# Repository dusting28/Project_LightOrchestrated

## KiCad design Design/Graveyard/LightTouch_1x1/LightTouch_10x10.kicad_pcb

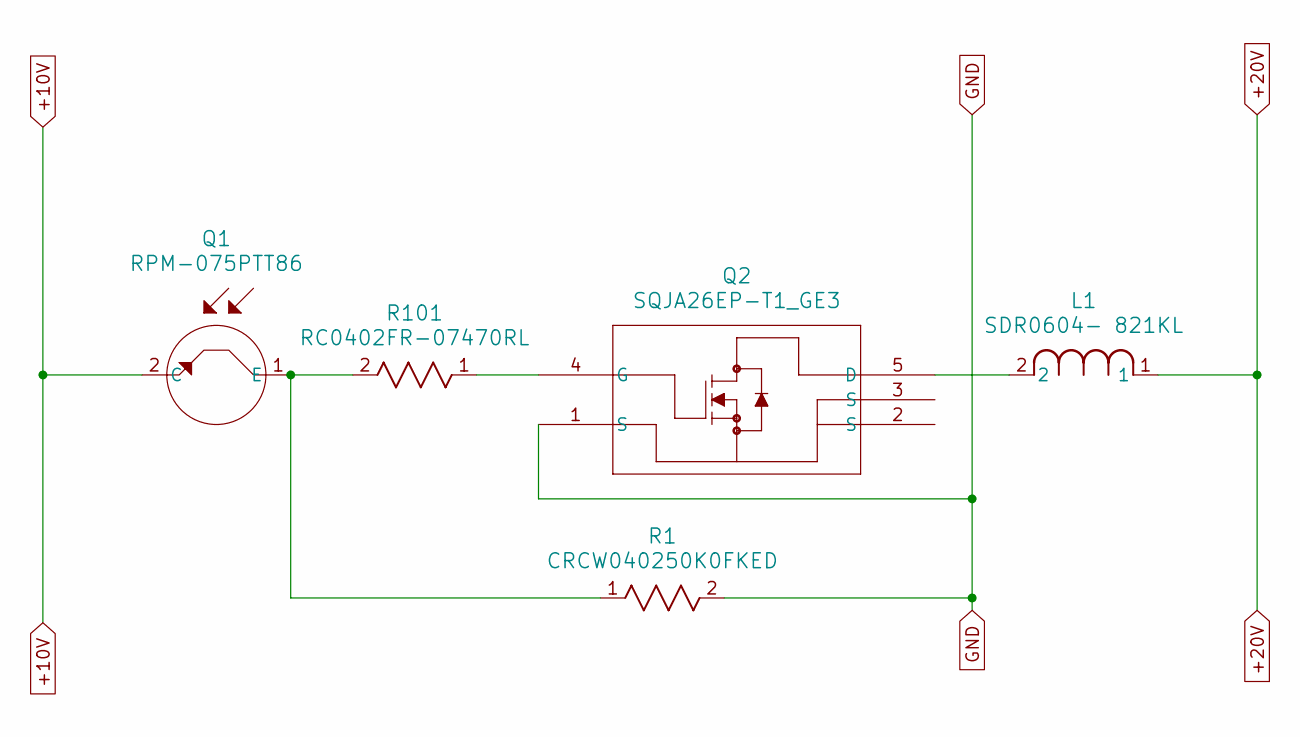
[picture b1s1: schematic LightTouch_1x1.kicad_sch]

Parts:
L1: SDR0604- 821KL; IND_BOURNS_SDR0604
Q1: RPM-075PTT86; TRANS_RPM-075P_ROM
Q2: SQJA26EP-T1_GE3; PowerPAK_SO-8L_3_VIS
R1: CRCW040250K0FKED; RES_CRCW0402_VIS
R101: RC0402FR-07470RL; RC0402N_YAG

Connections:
+10V: Q1.2 (C)
+20V: L1.1
GND: Q2.1 (S), R1.2
unnamed: Q1.1 (E), R1.1, R101.2
unnamed: L1.2, Q2.5 (D)
unnamed: Q2.4 (G), R101.1

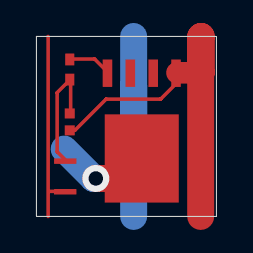
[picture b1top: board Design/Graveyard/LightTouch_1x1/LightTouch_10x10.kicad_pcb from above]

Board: 2 copper layers, 10.0 x 10.0 mm, 5 parts (1 on the bottom side), 4 nets.

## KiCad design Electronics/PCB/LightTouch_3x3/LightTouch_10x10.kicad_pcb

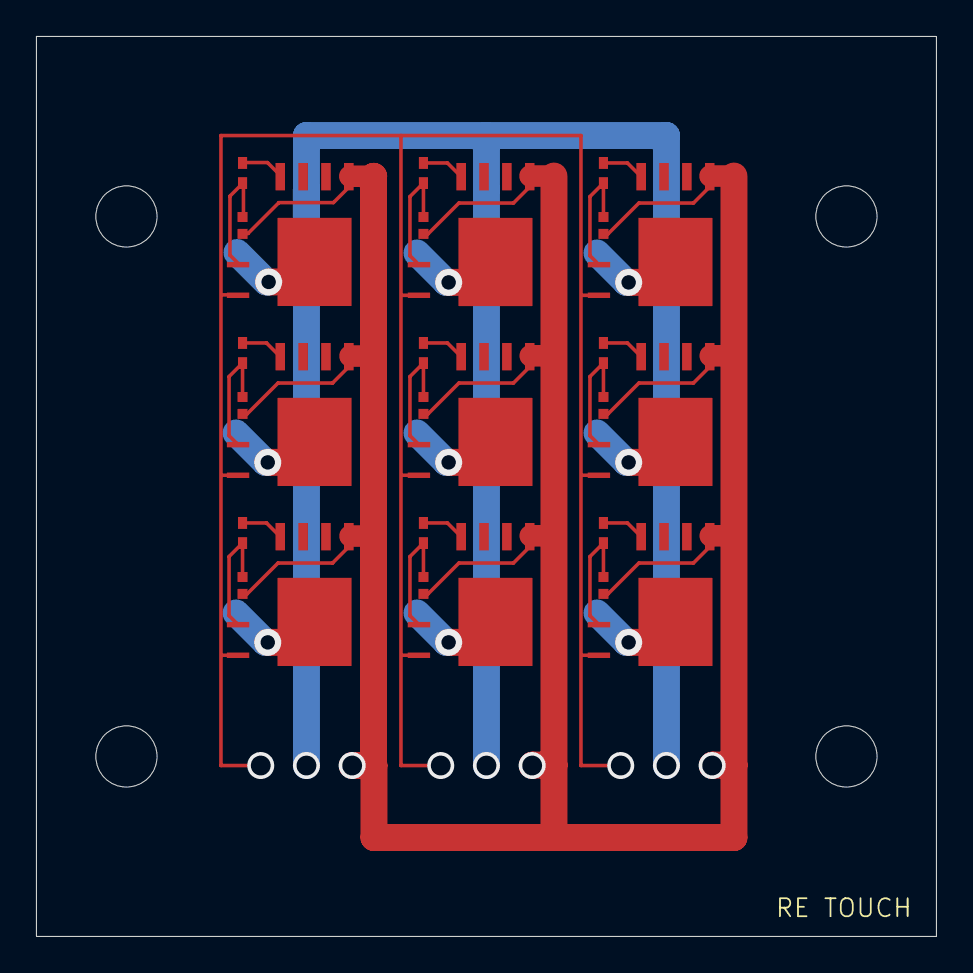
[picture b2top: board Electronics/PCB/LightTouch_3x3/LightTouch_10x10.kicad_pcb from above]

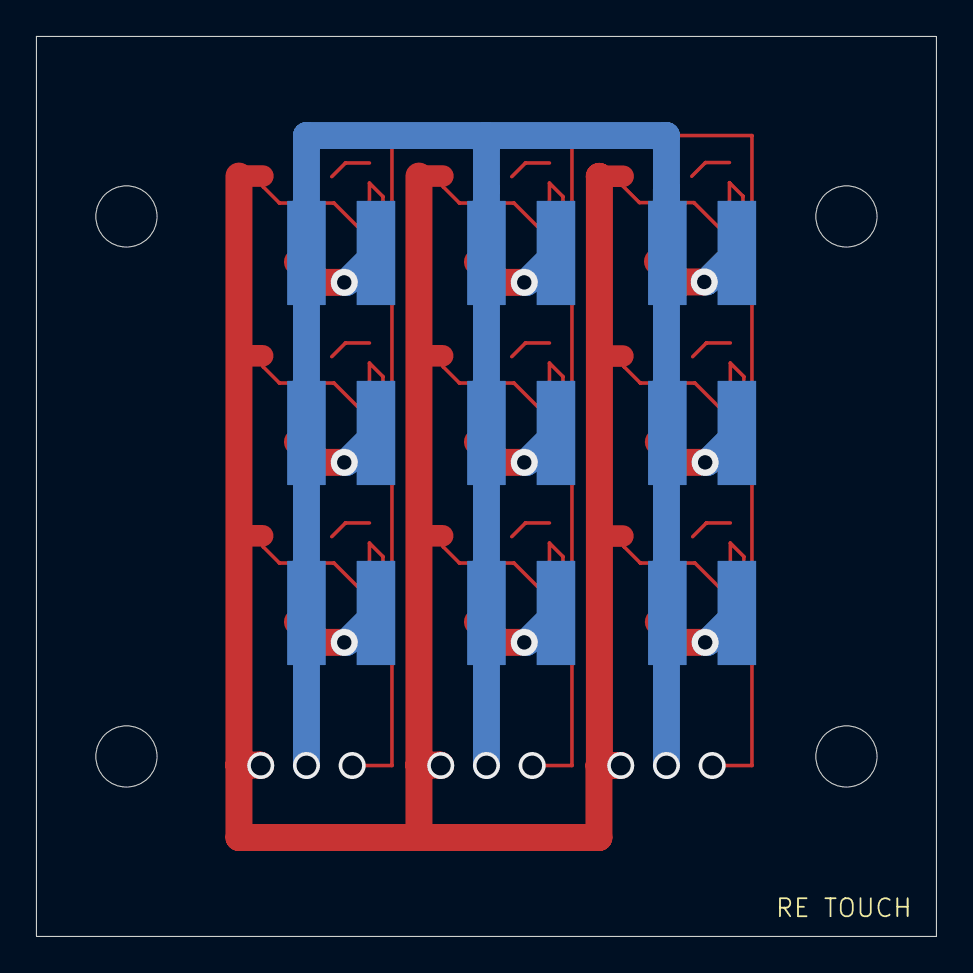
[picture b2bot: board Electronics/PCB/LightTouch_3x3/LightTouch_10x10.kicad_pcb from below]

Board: 2 copper layers, 50.0 x 50.0 mm, 45 parts (9 on the bottom side), 30 nets.

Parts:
L1, L2, L3, L4, L5, L6, L7, L8, L9: SDR0604- 821KL; IND_BOURNS_SDR0604
Q1, Q3, Q5, Q7, Q9, Q11, Q13, Q15, Q17: RPM-075PTT86; TRANS_RPM-075P_ROM
Q2, Q4, Q6, Q8, Q10, Q12, Q14, Q16, Q18: SQJA26EP-T1_GE3; PowerPAK_SO-8L_3_VIS
R1, R2, R3, R4, R5, R6, R7, R8, R9: CRCW040250K0FKED; RES_CRCW0402_VIS
R101, R102, R103, R104, R105, R106, R107, R108, R109: RC0402FR-07470RL; RC0402N_YAG

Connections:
+10V: Q1.2 (C), Q3.2 (C), Q5.2 (C), Q7.2 (C), Q9.2 (C), Q11.2 (C), Q13.2 (C), Q15.2 (C), Q17.2 (C)
+20V: L1.1, L2.1, L3.1, L4.1, L5.1, L6.1, L7.1, L8.1, L9.1
GND: Q2.1 (S), Q4.1 (S), Q6.1 (S), Q8.1 (S), Q10.1 (S), Q12.1 (S), Q14.1 (S), Q16.1 (S), Q18.1 (S), R1.2, R2.2, R3.2, R4.2, R5.2, R6.2, R7.2, R8.2, R9.2
unnamed: Q1.1 (E), R1.1, R101.2
unnamed: L1.2, Q2.5 (D)
unnamed: Q2.4 (G), R101.1
unnamed: Q3.1 (E), R2.1, R102.2
unnamed: L2.2, Q4.5 (D)
unnamed: Q4.4 (G), R102.1
unnamed: Q5.1 (E), R3.1, R103.2
unnamed: L3.2, Q6.5 (D)
unnamed: Q6.4 (G), R103.1
unnamed: Q7.1 (E), R4.1, R104.2
unnamed: L4.2, Q8.5 (D)
unnamed: Q8.4 (G), R104.1
unnamed: Q9.1 (E), R5.1, R105.2
unnamed: L5.2, Q10.5 (D)
unnamed: Q10.4 (G), R105.1
unnamed: Q11.1 (E), R6.1, R106.2
unnamed: L6.2, Q12.5 (D)
unnamed: Q12.4 (G), R106.1
unnamed: Q13.1 (E), R7.1, R107.2
unnamed: L7.2, Q14.5 (D)
unnamed: Q14.4 (G), R107.1
unnamed: Q15.1 (E), R8.1, R108.2
unnamed: L8.2, Q16.5 (D)
unnamed: Q16.4 (G), R108.1
unnamed: Q17.1 (E), R9.1, R109.2
unnamed: L9.2, Q18.5 (D)
unnamed: Q18.4 (G), R109.1

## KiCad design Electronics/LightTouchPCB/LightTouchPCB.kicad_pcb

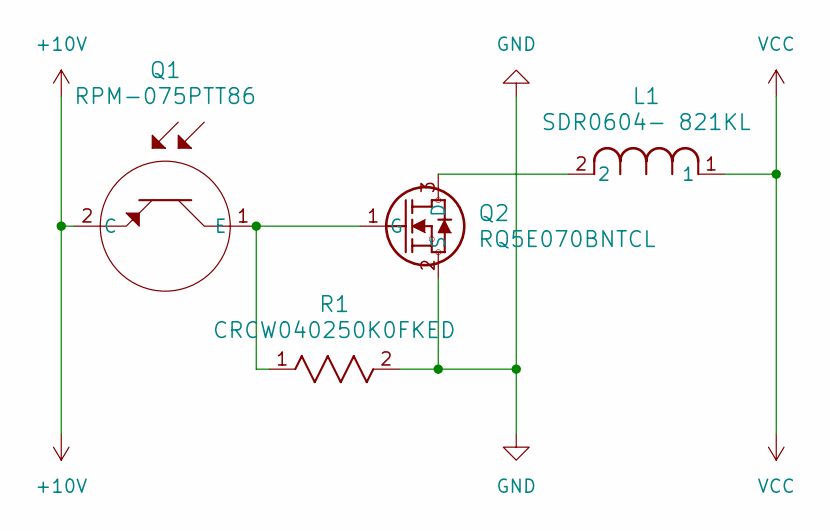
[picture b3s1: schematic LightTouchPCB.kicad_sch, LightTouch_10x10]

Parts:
L1: SDR0604- 821KL; IND_BOURNS_SDR0604
Q1: RPM-075PTT86; TRANS_RPM-075P_ROM
Q2: RQ5E070BNTCL; TRANS_RDR005N_ROM
R1: CRCW040250K0FKED; RES_CRCW0402_VIS

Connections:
+10V: Q1.2 (C)
GND: Q2.2 (S), R1.2
unnamed: Q1.1 (E), Q2.1 (G), R1.1
unnamed: L1.2, Q2.3 (D)
VCC: L1.1

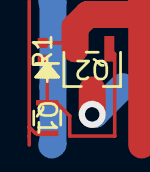
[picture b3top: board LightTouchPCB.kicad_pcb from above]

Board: 2 copper layers, 4 parts (1 on the bottom side), 3 nets.

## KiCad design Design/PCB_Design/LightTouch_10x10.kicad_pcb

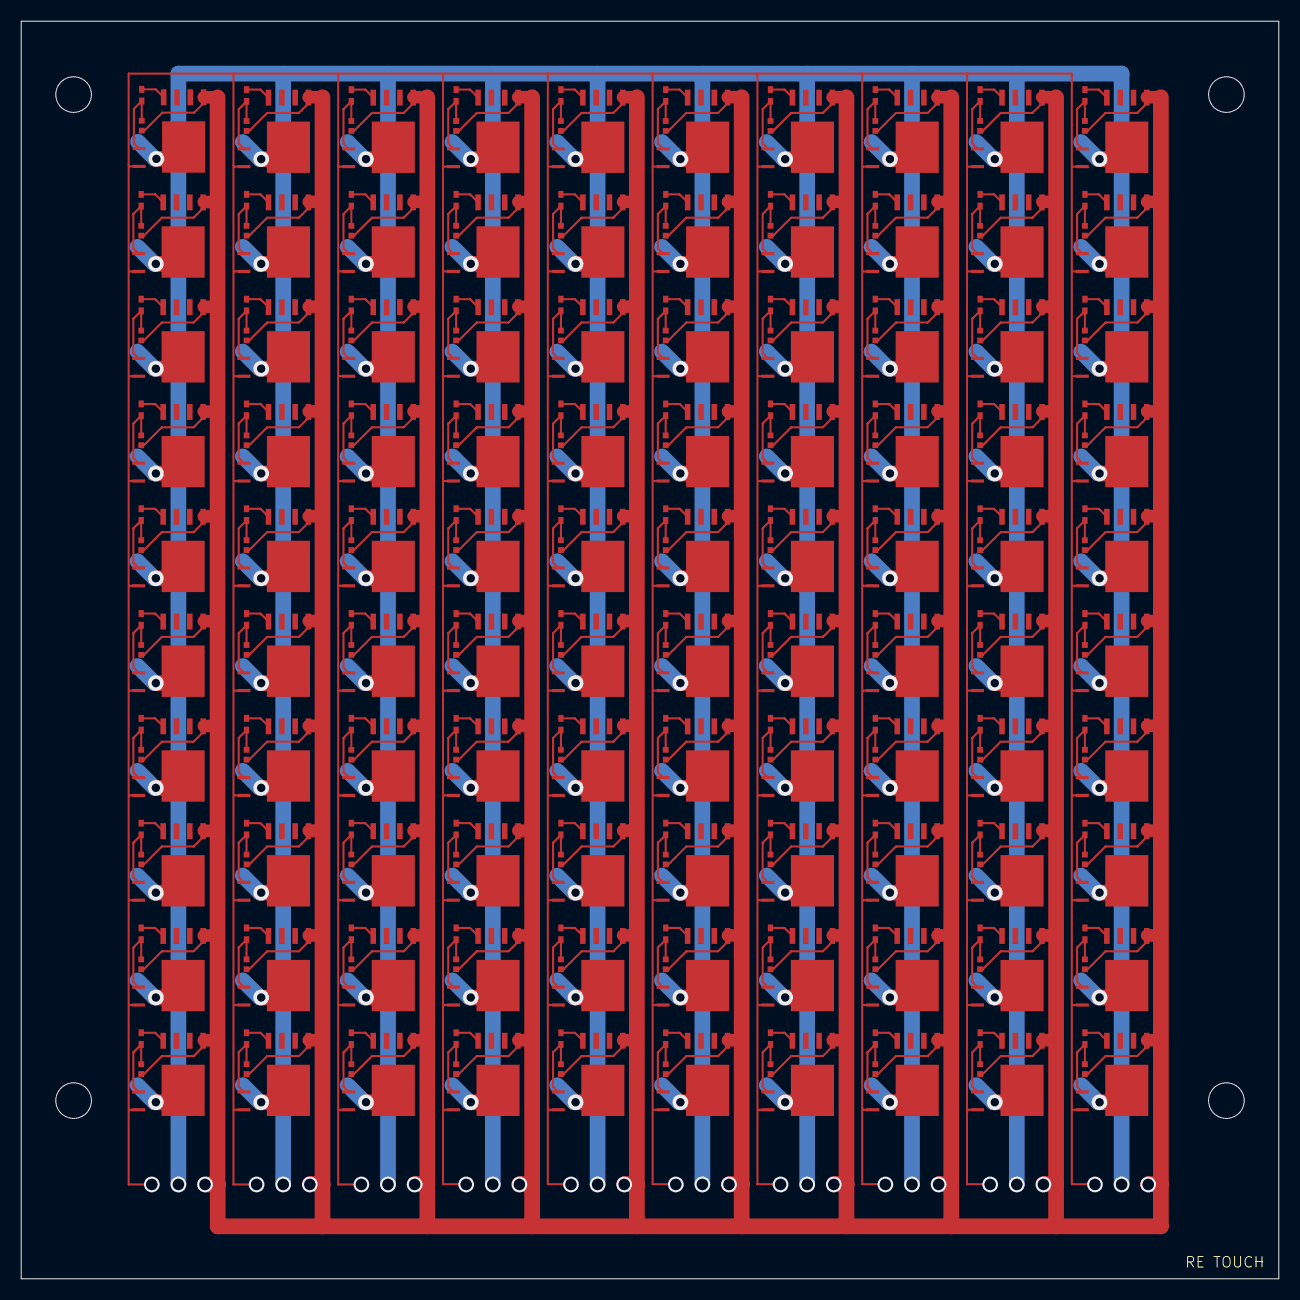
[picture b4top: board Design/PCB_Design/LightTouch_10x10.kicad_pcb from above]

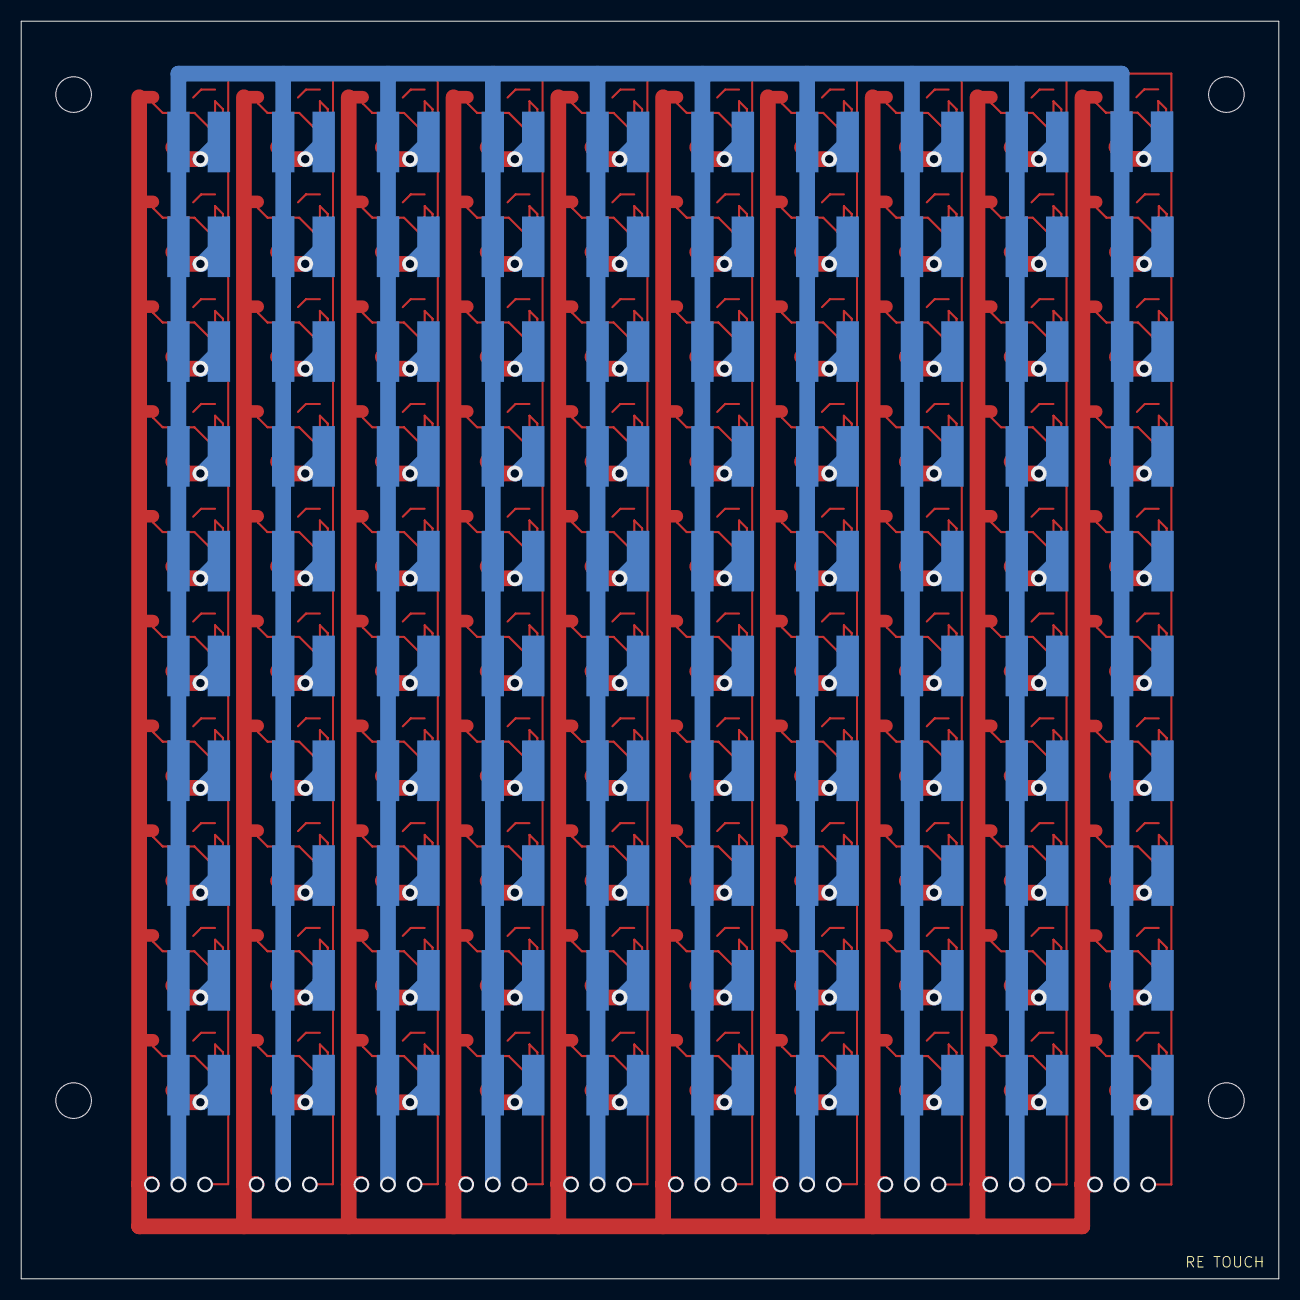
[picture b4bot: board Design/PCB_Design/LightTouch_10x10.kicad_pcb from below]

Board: 2 copper layers, 120.0 x 120.0 mm, 500 parts (100 on the bottom side), 303 nets.

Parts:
L1, L2, L3, L4, L5, L6, L7, L8, L9, L10, L11, L12, L13, L14, L15, L16, L17, L18, L19, L20, L21, L22, L23, L24, L25, L26, L27, L28, L29, L30, L31, L32, L33, L34, L35, L36, L37, L38, L39, L40, L41, L42, L43, L44, L45, L46, L47, L48, L49, L50, L51, L52, L53, L54, L55, L56, L57, L58, L59, L60, L61, L62, L63, L64, L65, L66, L67, L68, L69, L70, L71, L72, L73, L74, L75, L76, L77, L78, L79, L80, L81, L82, L83, L84, L85, L86, L87, L88, L89, L90, L91, L92, L93, L94, L95, L96, L97, L98, L99, L100: SDR0604- 821KL; IND_BOURNS_SDR0604
Q1, Q3, Q5, Q7, Q9, Q11, Q13, Q15, Q17, Q19, Q21, Q23, Q25, Q27, Q29, Q31, Q33, Q35, Q37, Q39, Q41, Q43, Q45, Q47, Q49, Q51, Q53, Q55, Q57, Q59, Q61, Q63, Q65, Q67, Q69, Q71, Q73, Q75, Q77, Q79, Q81, Q83, Q85, Q87, Q89, Q91, Q93, Q95, Q97, Q99, Q101, Q103, Q105, Q107, Q109, Q111, Q113, Q115, Q117, Q119, Q121, Q123, Q125, Q127, Q129, Q131, Q133, Q135, Q137, Q139, Q141, Q143, Q145, Q147, Q149, Q151, Q153, Q155, Q157, Q159, Q161, Q163, Q165, Q167, Q169, Q171, Q173, Q175, Q177, Q179, Q181, Q183, Q185, Q187, Q189, Q191, Q193, Q195, Q197, Q199: RPM-075PTT86; TRANS_RPM-075P_ROM
Q2, Q4, Q6, Q8, Q10, Q12, Q14, Q16, Q18, Q20, Q22, Q24, Q26, Q28, Q30, Q32, Q34, Q36, Q38, Q40, Q42, Q44, Q46, Q48, Q50, Q52, Q54, Q56, Q58, Q60, Q62, Q64, Q66, Q68, Q70, Q72, Q74, Q76, Q78, Q80, Q82, Q84, Q86, Q88, Q90, Q92, Q94, Q96, Q98, Q100, Q102, Q104, Q106, Q108, Q110, Q112, Q114, Q116, Q118, Q120, Q122, Q124, Q126, Q128, Q130, Q132, Q134, Q136, Q138, Q140, Q142, Q144, Q146, Q148, Q150, Q152, Q154, Q156, Q158, Q160, Q162, Q164, Q166, Q168, Q170, Q172, Q174, Q176, Q178, Q180, Q182, Q184, Q186, Q188, Q190, Q192, Q194, Q196, Q198, Q200: SQJA26EP-T1_GE3; PowerPAK_SO-8L_3_VIS
R1, R2, R3, R4, R5, R6, R7, R8, R9, R10, R11, R12, R13, R14, R15, R16, R17, R18, R19, R20, R21, R22, R23, R24, R25, R26, R27, R28, R29, R30, R31, R32, R33, R34, R35, R36, R37, R38, R39, R40, R41, R42, R43, R44, R45, R46, R47, R48, R49, R50, R51, R52, R53, R54, R55, R56, R57, R58, R59, R60, R61, R62, R63, R64, R65, R66, R67, R68, R69, R70, R71, R72, R73, R74, R75, R76, R77, R78, R79, R80, R81, R82, R83, R84, R85, R86, R87, R88, R89, R90, R91, R92, R93, R94, R95, R96, R97, R98, R99, R100: CRCW040250K0FKED; RES_CRCW0402_VIS
R101, R102, R103, R104, R105, R106, R107, R108, R109, R110, R111, R112, R113, R114, R115, R116, R117, R118, R119, R120, R121, R122, R123, R124, R125, R126, R127, R128, R129, R130, R131, R132, R133, R134, R135, R136, R137, R138, R139, R140, R141, R142, R143, R144, R145, R146, R147, R148, R149, R150, R151, R152, R153, R154, R155, R156, R157, R158, R159, R160, R161, R162, R163, R164, R165, R166, R167, R168, R169, R170, R171, R172, R173, R174, R175, R176, R177, R178, R179, R180, R181, R182, R183, R184, R185, R186, R187, R188, R189, R190, R191, R192, R193, R194, R195, R196, R197, R198, R199, R200: RC0402FR-07470RL; RC0402N_YAG

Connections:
+10V: Q1.2 (C), Q3.2 (C), Q5.2 (C), Q7.2 (C), Q9.2 (C), Q11.2 (C), Q13.2 (C), Q15.2 (C), Q17.2 (C), Q19.2 (C), Q21.2 (C), Q23.2 (C), Q25.2 (C), Q27.2 (C), Q29.2 (C), Q31.2 (C), Q33.2 (C), Q35.2 (C), Q37.2 (C), Q39.2 (C), Q41.2 (C), Q43.2 (C), Q45.2 (C), Q47.2 (C), Q49.2 (C), Q51.2 (C), Q53.2 (C), Q55.2 (C), Q57.2 (C), Q59.2 (C), Q61.2 (C), Q63.2 (C), Q65.2 (C), Q67.2 (C), Q69.2 (C), Q71.2 (C), Q73.2 (C), Q75.2 (C), Q77.2 (C), Q79.2 (C), Q81.2 (C), Q83.2 (C), Q85.2 (C), Q87.2 (C), Q89.2 (C), Q91.2 (C), Q93.2 (C), Q95.2 (C), Q97.2 (C), Q99.2 (C), Q101.2 (C), Q103.2 (C), Q105.2 (C), Q107.2 (C), Q109.2 (C), Q111.2 (C), Q113.2 (C), Q115.2 (C), Q117.2 (C), Q119.2 (C), Q121.2 (C), Q123.2 (C), Q125.2 (C), Q127.2 (C), Q129.2 (C), Q131.2 (C), Q133.2 (C), Q135.2 (C), Q137.2 (C), Q139.2 (C), Q141.2 (C), Q143.2 (C), Q145.2 (C), Q147.2 (C), Q149.2 (C), Q151.2 (C), Q153.2 (C), Q155.2 (C), Q157.2 (C), Q159.2 (C), Q161.2 (C), Q163.2 (C), Q165.2 (C), Q167.2 (C), Q169.2 (C), Q171.2 (C), Q173.2 (C), Q175.2 (C), Q177.2 (C), Q179.2 (C), Q181.2 (C), Q183.2 (C), Q185.2 (C), Q187.2 (C), Q189.2 (C), Q191.2 (C), Q193.2 (C), Q195.2 (C), Q197.2 (C), Q199.2 (C)
+20V: L1.1, L2.1, L3.1, L4.1, L5.1, L6.1, L7.1, L8.1, L9.1, L10.1, L11.1, L12.1, L13.1, L14.1, L15.1, L16.1, L17.1, L18.1, L19.1, L20.1, L21.1, L22.1, L23.1, L24.1, L25.1, L26.1, L27.1, L28.1, L29.1, L30.1, L31.1, L32.1, L33.1, L34.1, L35.1, L36.1, L37.1, L38.1, L39.1, L40.1, L41.1, L42.1, L43.1, L44.1, L45.1, L46.1, L47.1, L48.1, L49.1, L50.1, L51.1, L52.1, L53.1, L54.1, L55.1, L56.1, L57.1, L58.1, L59.1, L60.1, L61.1, L62.1, L63.1, L64.1, L65.1, L66.1, L67.1, L68.1, L69.1, L70.1, L71.1, L72.1, L73.1, L74.1, L75.1, L76.1, L77.1, L78.1, L79.1, L80.1, L81.1, L82.1, L83.1, L84.1, L85.1, L86.1, L87.1, L88.1, L89.1, L90.1, L91.1, L92.1, L93.1, L94.1, L95.1, L96.1, L97.1, L98.1, L99.1, L100.1
GND: Q2.1 (S), Q4.1 (S), Q6.1 (S), Q8.1 (S), Q10.1 (S), Q12.1 (S), Q14.1 (S), Q16.1 (S), Q18.1 (S), Q20.1 (S), Q22.1 (S), Q24.1 (S), Q26.1 (S), Q28.1 (S), Q30.1 (S), Q32.1 (S), Q34.1 (S), Q36.1 (S), Q38.1 (S), Q40.1 (S), Q42.1 (S), Q44.1 (S), Q46.1 (S), Q48.1 (S), Q50.1 (S), Q52.1 (S), Q54.1 (S), Q56.1 (S), Q58.1 (S), Q60.1 (S), Q62.1 (S), Q64.1 (S), Q66.1 (S), Q68.1 (S), Q70.1 (S), Q72.1 (S), Q74.1 (S), Q76.1 (S), Q78.1 (S), Q80.1 (S), Q82.1 (S), Q84.1 (S), Q86.1 (S), Q88.1 (S), Q90.1 (S), Q92.1 (S), Q94.1 (S), Q96.1 (S), Q98.1 (S), Q100.1 (S), Q102.1 (S), Q104.1 (S), Q106.1 (S), Q108.1 (S), Q110.1 (S), Q112.1 (S), Q114.1 (S), Q116.1 (S), Q118.1 (S), Q120.1 (S), Q122.1 (S), Q124.1 (S), Q126.1 (S), Q128.1 (S), Q130.1 (S), Q132.1 (S), Q134.1 (S), Q136.1 (S), Q138.1 (S), Q140.1 (S), Q142.1 (S), Q144.1 (S), Q146.1 (S), Q148.1 (S), Q150.1 (S), Q152.1 (S), Q154.1 (S), Q156.1 (S), Q158.1 (S), Q160.1 (S), Q162.1 (S), Q164.1 (S), Q166.1 (S), Q168.1 (S), Q170.1 (S), Q172.1 (S), Q174.1 (S), Q176.1 (S), Q178.1 (S), Q180.1 (S), Q182.1 (S), Q184.1 (S), Q186.1 (S), Q188.1 (S), Q190.1 (S), Q192.1 (S), Q194.1 (S), Q196.1 (S), Q198.1 (S), Q200.1 (S), R1.2, R2.2, R3.2, R4.2, R5.2, R6.2, R7.2, R8.2, R9.2, R10.2, R11.2, R12.2, R13.2, R14.2, R15.2, R16.2, R17.2, R18.2, R19.2, R20.2, R21.2, R22.2, R23.2, R24.2, R25.2, R26.2, R27.2, R28.2, R29.2, R30.2, R31.2, R32.2, R33.2, R34.2, R35.2, R36.2, R37.2, R38.2, R39.2, R40.2, R41.2, R42.2, R43.2, R44.2, R45.2, R46.2, R47.2, R48.2, R49.2, R50.2, R51.2, R52.2, R53.2, R54.2, R55.2, R56.2, R57.2, R58.2, R59.2, R60.2, R61.2, R62.2, R63.2, R64.2, R65.2, R66.2, R67.2, R68.2, R69.2, R70.2, R71.2, R72.2, R73.2, R74.2, R75.2, R76.2, R77.2, R78.2, R79.2, R80.2, R81.2, R82.2, R83.2, R84.2, R85.2, R86.2, R87.2, R88.2, R89.2, R90.2, R91.2, R92.2, R93.2, R94.2, R95.2, R96.2, R97.2, R98.2, R99.2, R100.2
unnamed: Q1.1 (E), R1.1, R101.2
unnamed: L1.2, Q2.5 (D)
unnamed: Q2.4 (G), R101.1
unnamed: Q3.1 (E), R2.1, R102.2
unnamed: L2.2, Q4.5 (D)
unnamed: Q4.4 (G), R102.1
unnamed: Q5.1 (E), R3.1, R103.2
unnamed: L3.2, Q6.5 (D)
unnamed: Q6.4 (G), R103.1
unnamed: Q7.1 (E), R4.1, R104.2
unnamed: L4.2, Q8.5 (D)
unnamed: Q8.4 (G), R104.1
unnamed: Q9.1 (E), R5.1, R105.2
unnamed: L5.2, Q10.5 (D)
unnamed: Q10.4 (G), R105.1
unnamed: Q11.1 (E), R6.1, R106.2
unnamed: L6.2, Q12.5 (D)
unnamed: Q12.4 (G), R106.1
unnamed: Q13.1 (E), R7.1, R107.2
unnamed: L7.2, Q14.5 (D)
unnamed: Q14.4 (G), R107.1
unnamed: Q15.1 (E), R8.1, R108.2
unnamed: L8.2, Q16.5 (D)
unnamed: Q16.4 (G), R108.1
unnamed: Q17.1 (E), R9.1, R109.2
unnamed: L9.2, Q18.5 (D)
unnamed: Q18.4 (G), R109.1
unnamed: Q19.1 (E), R10.1, R110.2
unnamed: L10.2, Q20.5 (D)
unnamed: Q20.4 (G), R110.1
unnamed: Q21.1 (E), R11.1, R111.2
unnamed: L11.2, Q22.5 (D)
unnamed: Q22.4 (G), R111.1
unnamed: Q23.1 (E), R12.1, R112.2
unnamed: L12.2, Q24.5 (D)
unnamed: Q24.4 (G), R112.1
unnamed: Q25.1 (E), R13.1, R113.2
unnamed: L13.2, Q26.5 (D)
unnamed: Q26.4 (G), R113.1
unnamed: Q27.1 (E), R14.1, R114.2
unnamed: L14.2, Q28.5 (D)
unnamed: Q28.4 (G), R114.1
unnamed: Q29.1 (E), R15.1, R115.2
unnamed: L15.2, Q30.5 (D)
unnamed: Q30.4 (G), R115.1
unnamed: Q31.1 (E), R16.1, R116.2
unnamed: L16.2, Q32.5 (D)
unnamed: Q32.4 (G), R116.1
unnamed: Q33.1 (E), R17.1, R117.2
unnamed: L17.2, Q34.5 (D)
unnamed: Q34.4 (G), R117.1
unnamed: Q35.1 (E), R18.1, R118.2
unnamed: L18.2, Q36.5 (D)
unnamed: Q36.4 (G), R118.1
unnamed: Q37.1 (E), R19.1, R119.2
unnamed: L19.2, Q38.5 (D)
unnamed: Q38.4 (G), R119.1
unnamed: Q39.1 (E), R20.1, R120.2
unnamed: L20.2, Q40.5 (D)
unnamed: Q40.4 (G), R120.1
unnamed: Q41.1 (E), R21.1, R121.2
unnamed: L21.2, Q42.5 (D)
unnamed: Q42.4 (G), R121.1
unnamed: Q43.1 (E), R22.1, R122.2
unnamed: L22.2, Q44.5 (D)
unnamed: Q44.4 (G), R122.1
unnamed: Q45.1 (E), R23.1, R123.2
unnamed: L23.2, Q46.5 (D)
unnamed: Q46.4 (G), R123.1
unnamed: Q47.1 (E), R24.1, R124.2
unnamed: L24.2, Q48.5 (D)
unnamed: Q48.4 (G), R124.1
unnamed: Q49.1 (E), R25.1, R125.2
unnamed: L25.2, Q50.5 (D)
unnamed: Q50.4 (G), R125.1
unnamed: Q51.1 (E), R26.1, R126.2
unnamed: L26.2, Q52.5 (D)
unnamed: Q52.4 (G), R126.1
unnamed: Q53.1 (E), R27.1, R127.2
unnamed: L27.2, Q54.5 (D)
unnamed: Q54.4 (G), R127.1
unnamed: Q55.1 (E), R28.1, R128.2
unnamed: L28.2, Q56.5 (D)
unnamed: Q56.4 (G), R128.1
unnamed: Q57.1 (E), R29.1, R129.2
unnamed: L29.2, Q58.5 (D)
unnamed: Q58.4 (G), R129.1
unnamed: Q59.1 (E), R30.1, R130.2
unnamed: L30.2, Q60.5 (D)
unnamed: Q60.4 (G), R130.1
unnamed: Q61.1 (E), R31.1, R131.2
unnamed: L31.2, Q62.5 (D)
unnamed: Q62.4 (G), R131.1
unnamed: Q63.1 (E), R32.1, R132.2
unnamed: L32.2, Q64.5 (D)
unnamed: Q64.4 (G), R132.1
unnamed: Q65.1 (E), R33.1, R133.2
unnamed: L33.2, Q66.5 (D)
unnamed: Q66.4 (G), R133.1
unnamed: Q67.1 (E), R34.1, R134.2
unnamed: L34.2, Q68.5 (D)
unnamed: Q68.4 (G), R134.1
unnamed: Q69.1 (E), R35.1, R135.2
unnamed: L35.2, Q70.5 (D)
unnamed: Q70.4 (G), R135.1
unnamed: Q71.1 (E), R36.1, R136.2
unnamed: L36.2, Q72.5 (D)
unnamed: Q72.4 (G), R136.1
unnamed: Q73.1 (E), R37.1, R137.2
unnamed: L37.2, Q74.5 (D)
unnamed: Q74.4 (G), R137.1
unnamed: Q75.1 (E), R38.1, R138.2
unnamed: L38.2, Q76.5 (D)
unnamed: Q76.4 (G), R138.1
unnamed: Q77.1 (E), R39.1, R139.2
unnamed: L39.2, Q78.5 (D)
unnamed: Q78.4 (G), R139.1
unnamed: Q79.1 (E), R40.1, R140.2
unnamed: L40.2, Q80.5 (D)
unnamed: Q80.4 (G), R140.1
unnamed: Q81.1 (E), R41.1, R141.2
unnamed: L41.2, Q82.5 (D)
unnamed: Q82.4 (G), R141.1
unnamed: Q83.1 (E), R42.1, R142.2
unnamed: L42.2, Q84.5 (D)
unnamed: Q84.4 (G), R142.1
unnamed: Q85.1 (E), R43.1, R143.2
unnamed: L43.2, Q86.5 (D)
unnamed: Q86.4 (G), R143.1
unnamed: Q87.1 (E), R44.1, R144.2
unnamed: L44.2, Q88.5 (D)
unnamed: Q88.4 (G), R144.1
unnamed: Q89.1 (E), R45.1, R145.2
unnamed: L45.2, Q90.5 (D)
unnamed: Q90.4 (G), R145.1
unnamed: Q91.1 (E), R46.1, R146.2
unnamed: L46.2, Q92.5 (D)
unnamed: Q92.4 (G), R146.1
unnamed: Q93.1 (E), R47.1, R147.2
unnamed: L47.2, Q94.5 (D)
unnamed: Q94.4 (G), R147.1
unnamed: Q95.1 (E), R48.1, R148.2
unnamed: L48.2, Q96.5 (D)
unnamed: Q96.4 (G), R148.1
unnamed: Q97.1 (E), R49.1, R149.2
unnamed: L49.2, Q98.5 (D)
unnamed: Q98.4 (G), R149.1
unnamed: Q99.1 (E), R50.1, R150.2
unnamed: L50.2, Q100.5 (D)
unnamed: Q100.4 (G), R150.1
unnamed: Q101.1 (E), R51.1, R151.2
unnamed: L51.2, Q102.5 (D)
unnamed: Q102.4 (G), R151.1
unnamed: Q103.1 (E), R52.1, R152.2
unnamed: L52.2, Q104.5 (D)
unnamed: Q104.4 (G), R152.1
unnamed: Q105.1 (E), R53.1, R153.2
unnamed: L53.2, Q106.5 (D)
unnamed: Q106.4 (G), R153.1
unnamed: Q107.1 (E), R54.1, R154.2
unnamed: L54.2, Q108.5 (D)
unnamed: Q108.4 (G), R154.1
unnamed: Q109.1 (E), R55.1, R155.2
unnamed: L55.2, Q110.5 (D)
unnamed: Q110.4 (G), R155.1
unnamed: Q111.1 (E), R56.1, R156.2
unnamed: L56.2, Q112.5 (D)
unnamed: Q112.4 (G), R156.1
unnamed: Q113.1 (E), R57.1, R157.2
unnamed: L57.2, Q114.5 (D)
unnamed: Q114.4 (G), R157.1
unnamed: Q115.1 (E), R58.1, R158.2
unnamed: L58.2, Q116.5 (D)
unnamed: Q116.4 (G), R158.1
unnamed: Q117.1 (E), R59.1, R159.2
unnamed: L59.2, Q118.5 (D)
unnamed: Q118.4 (G), R159.1
unnamed: Q119.1 (E), R60.1, R160.2
unnamed: L60.2, Q120.5 (D)
unnamed: Q120.4 (G), R160.1
unnamed: Q121.1 (E), R61.1, R161.2
unnamed: L61.2, Q122.5 (D)
unnamed: Q122.4 (G), R161.1
unnamed: Q123.1 (E), R62.1, R162.2
unnamed: L62.2, Q124.5 (D)
unnamed: Q124.4 (G), R162.1
unnamed: Q125.1 (E), R63.1, R163.2
unnamed: L63.2, Q126.5 (D)
unnamed: Q126.4 (G), R163.1
unnamed: Q127.1 (E), R64.1, R164.2
unnamed: L64.2, Q128.5 (D)
unnamed: Q128.4 (G), R164.1
unnamed: Q129.1 (E), R65.1, R165.2
unnamed: L65.2, Q130.5 (D)
unnamed: Q130.4 (G), R165.1
unnamed: Q131.1 (E), R66.1, R166.2
unnamed: L66.2, Q132.5 (D)
unnamed: Q132.4 (G), R166.1
unnamed: Q133.1 (E), R67.1, R167.2
unnamed: L67.2, Q134.5 (D)
unnamed: Q134.4 (G), R167.1
unnamed: Q135.1 (E), R68.1, R168.2
unnamed: L68.2, Q136.5 (D)
unnamed: Q136.4 (G), R168.1
unnamed: Q137.1 (E), R69.1, R169.2
unnamed: L69.2, Q138.5 (D)
unnamed: Q138.4 (G), R169.1
unnamed: Q139.1 (E), R70.1, R170.2
unnamed: L70.2, Q140.5 (D)
unnamed: Q140.4 (G), R170.1
unnamed: Q141.1 (E), R71.1, R171.2
unnamed: L71.2, Q142.5 (D)
unnamed: Q142.4 (G), R171.1
unnamed: Q143.1 (E), R72.1, R172.2
unnamed: L72.2, Q144.5 (D)
unnamed: Q144.4 (G), R172.1
unnamed: Q145.1 (E), R73.1, R173.2
unnamed: L73.2, Q146.5 (D)
unnamed: Q146.4 (G), R173.1
unnamed: Q147.1 (E), R74.1, R174.2
unnamed: L74.2, Q148.5 (D)
unnamed: Q148.4 (G), R174.1
unnamed: Q149.1 (E), R75.1, R175.2
unnamed: L75.2, Q150.5 (D)
unnamed: Q150.4 (G), R175.1
unnamed: Q151.1 (E), R76.1, R176.2
unnamed: L76.2, Q152.5 (D)
unnamed: Q152.4 (G), R176.1
unnamed: Q153.1 (E), R77.1, R177.2
unnamed: L77.2, Q154.5 (D)
unnamed: Q154.4 (G), R177.1
unnamed: Q155.1 (E), R78.1, R178.2
unnamed: L78.2, Q156.5 (D)
unnamed: Q156.4 (G), R178.1
unnamed: Q157.1 (E), R79.1, R179.2
unnamed: L79.2, Q158.5 (D)
unnamed: Q158.4 (G), R179.1
unnamed: Q159.1 (E), R80.1, R180.2
unnamed: L80.2, Q160.5 (D)
unnamed: Q160.4 (G), R180.1
unnamed: Q161.1 (E), R81.1, R181.2
unnamed: L81.2, Q162.5 (D)
unnamed: Q162.4 (G), R181.1
unnamed: Q163.1 (E), R82.1, R182.2
unnamed: L82.2, Q164.5 (D)
unnamed: Q164.4 (G), R182.1
unnamed: Q165.1 (E), R83.1, R183.2
unnamed: L83.2, Q166.5 (D)
unnamed: Q166.4 (G), R183.1
unnamed: Q167.1 (E), R84.1, R184.2
unnamed: L84.2, Q168.5 (D)
unnamed: Q168.4 (G), R184.1
unnamed: Q169.1 (E), R85.1, R185.2
unnamed: L85.2, Q170.5 (D)
unnamed: Q170.4 (G), R185.1
unnamed: Q171.1 (E), R86.1, R186.2
unnamed: L86.2, Q172.5 (D)
unnamed: Q172.4 (G), R186.1
unnamed: Q173.1 (E), R87.1, R187.2
unnamed: L87.2, Q174.5 (D)
unnamed: Q174.4 (G), R187.1
unnamed: Q175.1 (E), R88.1, R188.2
unnamed: L88.2, Q176.5 (D)
unnamed: Q176.4 (G), R188.1
unnamed: Q177.1 (E), R89.1, R189.2
unnamed: L89.2, Q178.5 (D)
unnamed: Q178.4 (G), R189.1
unnamed: Q179.1 (E), R90.1, R190.2
unnamed: L90.2, Q180.5 (D)
unnamed: Q180.4 (G), R190.1
unnamed: Q181.1 (E), R91.1, R191.2
unnamed: L91.2, Q182.5 (D)
unnamed: Q182.4 (G), R191.1
unnamed: Q183.1 (E), R92.1, R192.2
unnamed: L92.2, Q184.5 (D)
unnamed: Q184.4 (G), R192.1
unnamed: Q185.1 (E), R93.1, R193.2
unnamed: L93.2, Q186.5 (D)
unnamed: Q186.4 (G), R193.1
unnamed: Q187.1 (E), R94.1, R194.2
unnamed: L94.2, Q188.5 (D)
unnamed: Q188.4 (G), R194.1
unnamed: Q189.1 (E), R95.1, R195.2
unnamed: L95.2, Q190.5 (D)
unnamed: Q190.4 (G), R195.1
unnamed: Q191.1 (E), R96.1, R196.2
unnamed: L96.2, Q192.5 (D)
unnamed: Q192.4 (G), R196.1
unnamed: Q193.1 (E), R97.1, R197.2
unnamed: L97.2, Q194.5 (D)
unnamed: Q194.4 (G), R197.1
unnamed: Q195.1 (E), R98.1, R198.2
unnamed: L98.2, Q196.5 (D)
unnamed: Q196.4 (G), R198.1
unnamed: Q197.1 (E), R99.1, R199.2
unnamed: L99.2, Q198.5 (D)
unnamed: Q198.4 (G), R199.1
unnamed: Q199.1 (E), R100.1, R200.2
unnamed: L100.2, Q200.5 (D)
unnamed: Q200.4 (G), R200.1

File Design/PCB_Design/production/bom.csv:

Designator,Footprint,Quantity,Value,LCSC Part #
"L1, L10, L100, L11, L12, L13, L14, L15, L16, L17, L18, L19, L2, L20, L21, L22, L23, L24, L25, L26, L27, L28, L29, L3, L30, L31, L32, L33, L34, L35, L36, L37, L38, L39, L4, L40, L41, L42, L43, L44, L45, L46, L47, L48, L49, L5, L50, L51, L52, L53, L54, L55, L56, L57, L58, L59, L6, L60, L61, L62, L63, L64, L65, L66, L67, L68, L69, L7, L70, L71, L72, L73, L74, L75, L76, L77, L78, L79, L8, L80, L81, L82, L83, L84, L85, L86, L87, L88, L89, L9, L90, L91, L92, L93, L94, L95, L96, L97, L98, L99",IND_BOURNS_SDR0604,100,SDR0604- 821KL,
"Q1, Q101, Q103, Q105, Q107, Q109, Q11, Q111, Q113, Q115, Q117, Q119, Q121, Q123, Q125, Q127, Q129, Q13, Q131, Q133, Q135, Q137, Q139, Q141, Q143, Q145, Q147, Q149, Q15, Q151, Q153, Q155, Q157, Q159, Q161, Q163, Q165, Q167, Q169, Q17, Q171, Q173, Q175, Q177, Q179, Q181, Q183, Q185, Q187, Q189, Q19, Q191, Q193, Q195, Q197, Q199, Q21, Q23, Q25, Q27, Q29, Q3, Q31, Q33, Q35, Q37, Q39, Q41, Q43, Q45, Q47, Q49, Q5, Q51, Q53, Q55, Q57, Q59, Q61, Q63, Q65, Q67, Q69, Q7, Q71, Q73, Q75, Q77, Q79, Q81, Q83, Q85, Q87, Q89, Q9, Q91, Q93, Q95, Q97, Q99",TRANS_RPM-075P_ROM,100,RPM-075PTT86,
"Q10, Q100, Q102, Q104, Q106, Q108, Q110, Q112, Q114, Q116, Q118, Q12, Q120, Q122, Q124, Q126, Q128, Q130, Q132, Q134, Q136, Q138, Q14, Q140, Q142, Q144, Q146, Q148, Q150, Q152, Q154, Q156, Q158, Q16, Q160, Q162, Q164, Q166, Q168, Q170, Q172, Q174, Q176, Q178, Q18, Q180, Q182, Q184, Q186, Q188, Q190, Q192, Q194, Q196, Q198, Q2, Q20, Q200, Q22, Q24, Q26, Q28, Q30, Q32, Q34, Q36, Q38, Q4, Q40, Q42, Q44, Q46, Q48, Q50, Q52, Q54, Q56, Q58, Q6, Q60, Q62, Q64, Q66, Q68, Q70, Q72, Q74, Q76, Q78, Q8, Q80, Q82, Q84, Q86, Q88, Q90, Q92, Q94, Q96, Q98",PowerPAK_SO-8L_3_VIS,100,SQJA26EP-T1_GE3,
"R1, R10, R100, R11, R12, R13, R14, R15, R16, R17, R18, R19, R2, R20, R21, R22, R23, R24, R25, R26, R27, R28, R29, R3, R30, R31, R32, R33, R34, R35, R36, R37, R38, R39, R4, R40, R41, R42, R43, R44, R45, R46, R47, R48, R49, R5, R50, R51, R52, R53, R54, R55, R56, R57, R58, R59, R6, R60, R61, R62, R63, R64, R65, R66, R67, R68, R69, R7, R70, R71, R72, R73, R74, R75, R76, R77, R78, R79, R8, R80, R81, R82, R83, R84, R85, R86, R87, R88, R89, R9, R90, R91, R92, R93, R94, R95, R96, R97, R98, R99",RES_CRCW0402_VIS,100,CRCW040250K0FKED,
"R101, R102, R103, R104, R105, R106, R107, R108, R109, R110, R111, R112, R113, R114, R115, R116, R117, R118, R119, R120, R121, R122, R123, R124, R125, R126, R127, R128, R129, R130, R131, R132, R133, R134, R135, R136, R137, R138, R139, R140, R141, R142, R143, R144, R145, R146, R147, R148, R149, R150, R151, R152, R153, R154, R155, R156, R157, R158, R159, R160, R161, R162, R163, R164, R165, R166, R167, R168, R169, R170, R171, R172, R173, R174, R175, R176, R177, R178, R179, R180, R181, R182, R183, R184, R185, R186, R187, R188, R189, R190, R191, R192, R193, R194, R195, R196, R197, R198, R199, R200",RC0402N_YAG,100,RC0402FR-07470RL,
